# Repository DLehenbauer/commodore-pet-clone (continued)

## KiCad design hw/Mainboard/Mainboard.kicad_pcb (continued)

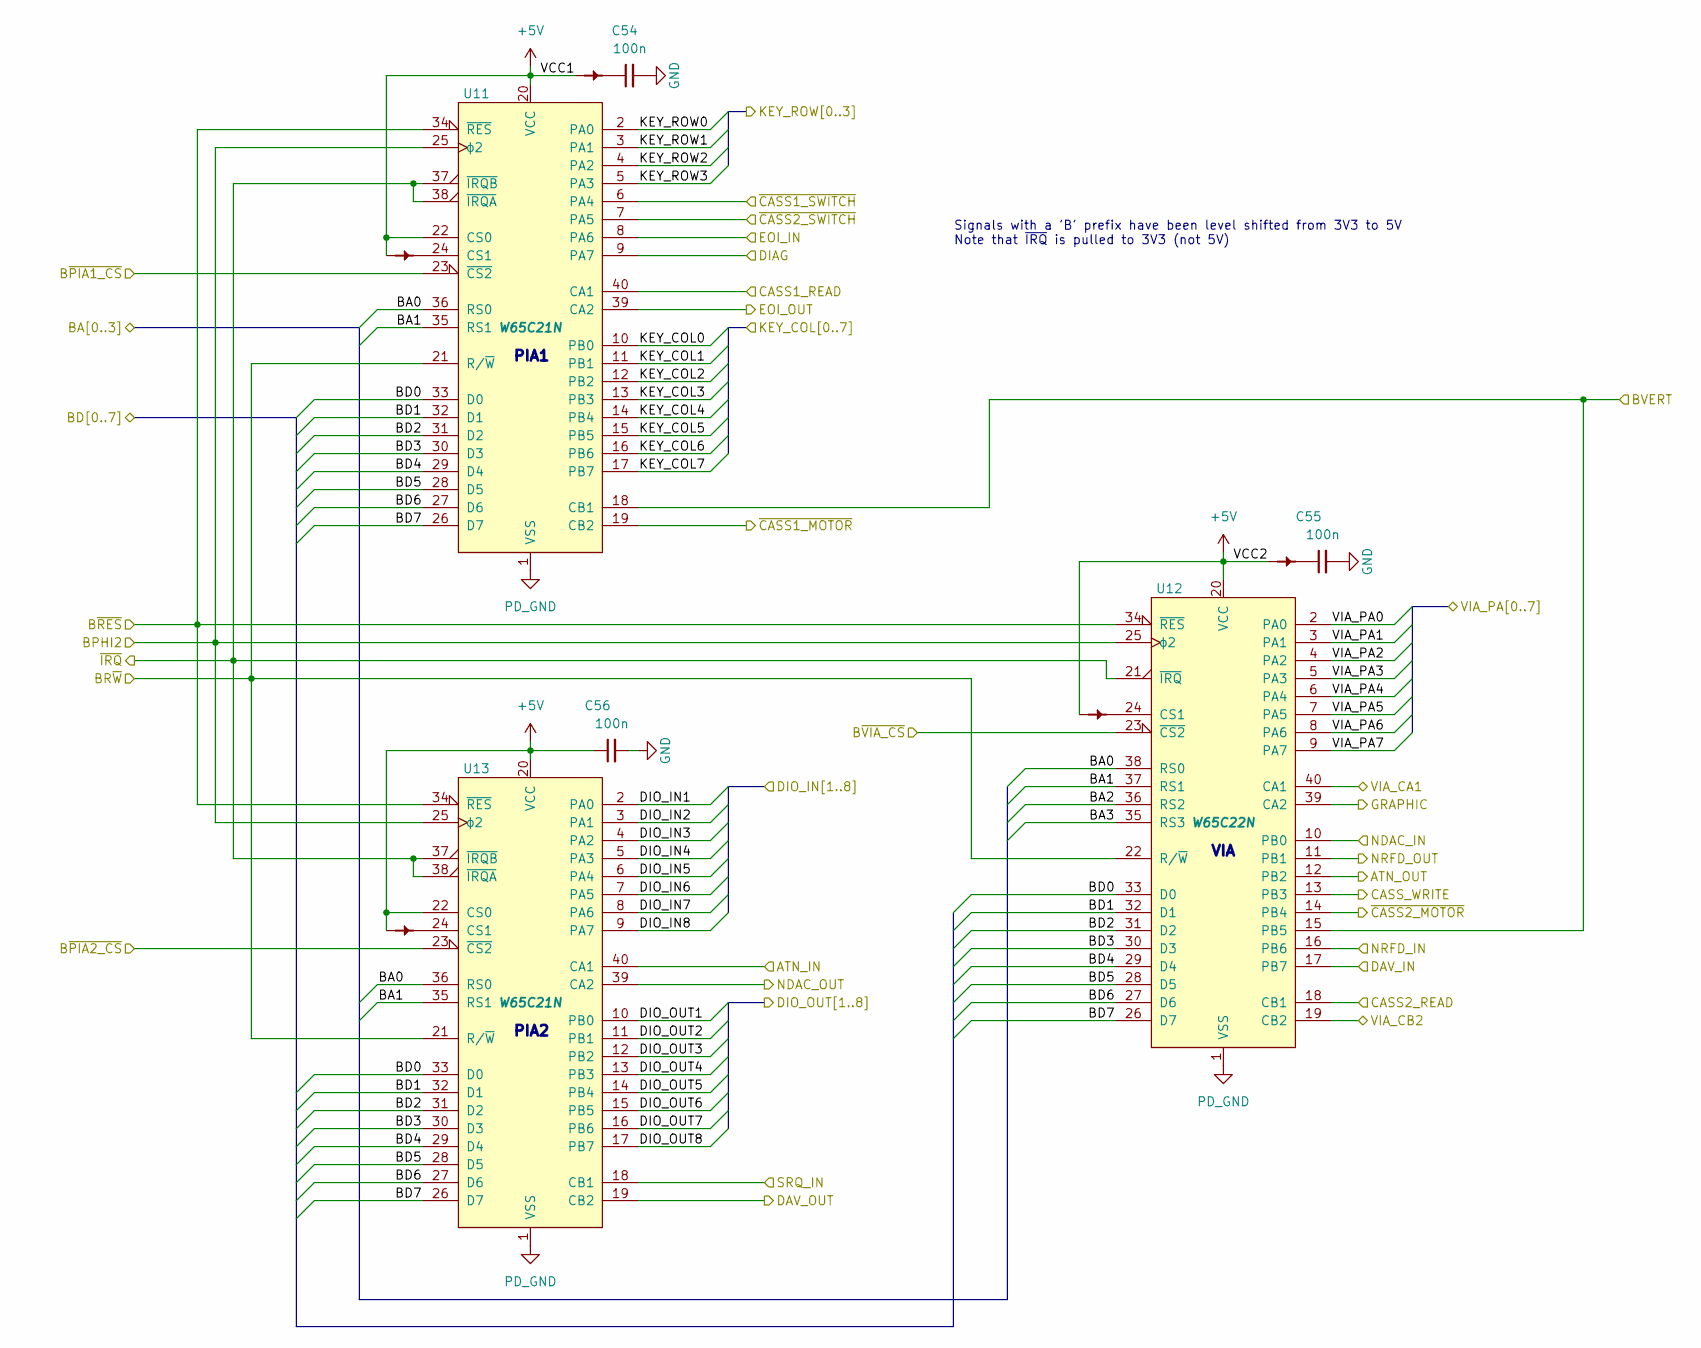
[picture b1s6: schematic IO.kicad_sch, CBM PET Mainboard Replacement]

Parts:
C54, C55, C56: 100n; C_0402_1005Metric; LCSC C307331
PT31, PT32, PT33, PT34, PT35: PowerTie_2; NetTie-2_SMD_Pad_1.6_to_0.4mm
U11, U13: W65C21N; DIP-40_W15.24mm_Socket; MOUSER 955-W65C21N6TPG-14,571-1-2199299-5
U12: W65C22N; DIP-40_W15.24mm_Socket; MOUSER 955-W65C22N6TPG-14,571-1-2199299-5

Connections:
+5V: C56.1, PT31.1, PT32.1, PT33.1, PT34.1, PT35.1, U11.20 (VCC), U11.22 (CS0), U12.20 (VCC), U13.20 (VCC), U13.22 (CS0); also elsewhere on the board
/CASS/CASS1_READ: U11.40 (CA1); also elsewhere on the board
/CASS/CASS2_READ: U12.18 (CB1); also elsewhere on the board
/CASS/CASS_WRITE: U12.13 (PB3); also elsewhere on the board
/CASS/~CASS1_MOTOR: U11.19 (CB2); also elsewhere on the board
/CASS/~CASS1_SWITCH: U11.6 (PA4); also elsewhere on the board
/CASS/~CASS2_MOTOR: U12.14 (PB4); also elsewhere on the board
/CASS/~CASS2_SWITCH: U11.7 (PA5); also elsewhere on the board
/IEEE/ATN_IN: U13.40 (CA1); also elsewhere on the board
/IEEE/ATN_OUT: U12.12 (PB2); also elsewhere on the board
/IEEE/DAV_IN: U12.17 (PB7); also elsewhere on the board
/IEEE/DAV_OUT: U13.19 (CB2); also elsewhere on the board
/IEEE/DIO_IN1: U13.2 (PA0); also elsewhere on the board
/IEEE/DIO_IN2: U13.3 (PA1); also elsewhere on the board
/IEEE/DIO_IN3: U13.4 (PA2); also elsewhere on the board
/IEEE/DIO_IN4: U13.5 (PA3); also elsewhere on the board
/IEEE/DIO_IN5: U13.6 (PA4); also elsewhere on the board
/IEEE/DIO_IN6: U13.7 (PA5); also elsewhere on the board
/IEEE/DIO_IN7: U13.8 (PA6); also elsewhere on the board
/IEEE/DIO_IN8: U13.9 (PA7); also elsewhere on the board
/IEEE/DIO_OUT1: U13.10 (PB0); also elsewhere on the board
/IEEE/DIO_OUT2: U13.11 (PB1); also elsewhere on the board
/IEEE/DIO_OUT3: U13.12 (PB2); also elsewhere on the board
/IEEE/DIO_OUT4: U13.13 (PB3); also elsewhere on the board
/IEEE/DIO_OUT5: U13.14 (PB4); also elsewhere on the board
/IEEE/DIO_OUT6: U13.15 (PB5); also elsewhere on the board
/IEEE/DIO_OUT7: U13.16 (PB6); also elsewhere on the board
/IEEE/DIO_OUT8: U13.17 (PB7); also elsewhere on the board
/IEEE/EOI_IN: U11.8 (PA6); also elsewhere on the board
/IEEE/EOI_OUT: U11.39 (CA2); also elsewhere on the board
/IEEE/IFC_OUT: U11.34 (~RES), U12.34 (~RES), U13.34 (~RES); also elsewhere on the board
/IEEE/NDAC_IN: U12.10 (PB0); also elsewhere on the board
/IEEE/NDAC_OUT: U13.39 (CA2); also elsewhere on the board
/IEEE/NRFD_IN: U12.16 (PB6); also elsewhere on the board
/IEEE/NRFD_OUT: U12.11 (PB1); also elsewhere on the board
/IEEE/SRQ_IN: U13.18 (CB1); also elsewhere on the board
/IO/BA0: U11.36 (RS0), U12.38 (RS0), U13.36 (RS0); also elsewhere on the board
/IO/BA1: U11.35 (RS1), U12.37 (RS1), U13.35 (RS1); also elsewhere on the board
/IO/BA2: U12.36 (RS2); also elsewhere on the board
/IO/BA3: U12.35 (RS3); also elsewhere on the board
/IO/BD0: U11.33 (D0), U12.33 (D0), U13.33 (D0); also elsewhere on the board
/IO/BD1: U11.32 (D1), U12.32 (D1), U13.32 (D1); also elsewhere on the board
/IO/BD2: U11.31 (D2), U12.31 (D2), U13.31 (D2); also elsewhere on the board
/IO/BD3: U11.30 (D3), U12.30 (D3), U13.30 (D3); also elsewhere on the board
/IO/BD4: U11.29 (D4), U12.29 (D4), U13.29 (D4); also elsewhere on the board
/IO/BD5: U11.28 (D5), U12.28 (D5), U13.28 (D5); also elsewhere on the board
/IO/BD6: U11.27 (D6), U12.27 (D6), U13.27 (D6); also elsewhere on the board
/IO/BD7: U11.26 (D7), U12.26 (D7), U13.26 (D7); also elsewhere on the board
/IO/BPHI2: U11.25 (ϕ2), U12.25 (ϕ2), U13.25 (ϕ2); also elsewhere on the board
/IO/BR~W: U11.21 (R/~W), U12.22 (R/~W), U13.21 (R/~W); also elsewhere on the board
/IO/BVERT: U11.18 (CB1), U12.15 (PB5); also elsewhere on the board
/IO/B~PIA1_CS: U11.23 (~CS2); also elsewhere on the board
/IO/B~PIA2_CS: U13.23 (~CS2); also elsewhere on the board
/IO/B~VIA_CS: U12.23 (~CS2); also elsewhere on the board
/IO/DIAG: U11.9 (PA7); also elsewhere on the board
/IO/GRAPHIC: U12.39 (CA2); also elsewhere on the board
/IO/KEY_COL0: U11.10 (PB0); also elsewhere on the board
/IO/KEY_COL1: U11.11 (PB1); also elsewhere on the board
/IO/KEY_COL2: U11.12 (PB2); also elsewhere on the board
/IO/KEY_COL3: U11.13 (PB3); also elsewhere on the board
/IO/KEY_COL4: U11.14 (PB4); also elsewhere on the board
/IO/KEY_COL5: U11.15 (PB5); also elsewhere on the board
/IO/KEY_COL6: U11.16 (PB6); also elsewhere on the board
/IO/KEY_COL7: U11.17 (PB7); also elsewhere on the board
/IO/KEY_ROW0: U11.2 (PA0); also elsewhere on the board
/IO/KEY_ROW1: U11.3 (PA1); also elsewhere on the board
/IO/KEY_ROW2: U11.4 (PA2); also elsewhere on the board
/IO/KEY_ROW3: U11.5 (PA3); also elsewhere on the board
/IO/VIA_CA1: U12.40 (CA1); also elsewhere on the board
/IO/VIA_CB2: U12.19 (CB2); also elsewhere on the board
/IO/VIA_PA0: U12.2 (PA0); also elsewhere on the board
/IO/VIA_PA1: U12.3 (PA1); also elsewhere on the board
/IO/VIA_PA2: U12.4 (PA2); also elsewhere on the board
/IO/VIA_PA3: U12.5 (PA3); also elsewhere on the board
/IO/VIA_PA4: U12.6 (PA4); also elsewhere on the board
/IO/VIA_PA5: U12.7 (PA5); also elsewhere on the board
/IO/VIA_PA6: U12.8 (PA6); also elsewhere on the board
/IO/VIA_PA7: U12.9 (PA7); also elsewhere on the board
/MAGIC/FPGA/~IRQ: U11.37 (~IRQB), U11.38 (~IRQA), U12.21 (~IRQ), U13.37 (~IRQB), U13.38 (~IRQA); also elsewhere on the board
GND: C54.2, C55.2, C56.2; also elsewhere on the board
unnamed: C54.1, PT31.2
unnamed: C55.1, PT33.2
unnamed: PT32.2, U11.24 (CS1)
unnamed: PT34.2, U12.24 (CS1)
unnamed: PT35.2, U13.24 (CS1)
PD_GND: U11.1 (VSS), U12.1 (VSS), U13.1 (VSS); also elsewhere on the board

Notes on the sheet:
PIA1
PIA2
Signals with a 'B' prefix have been level shifted from 3V3 to 5V Note that ~{IRQ} is pulled to 3V3 (not 5V)
VIA

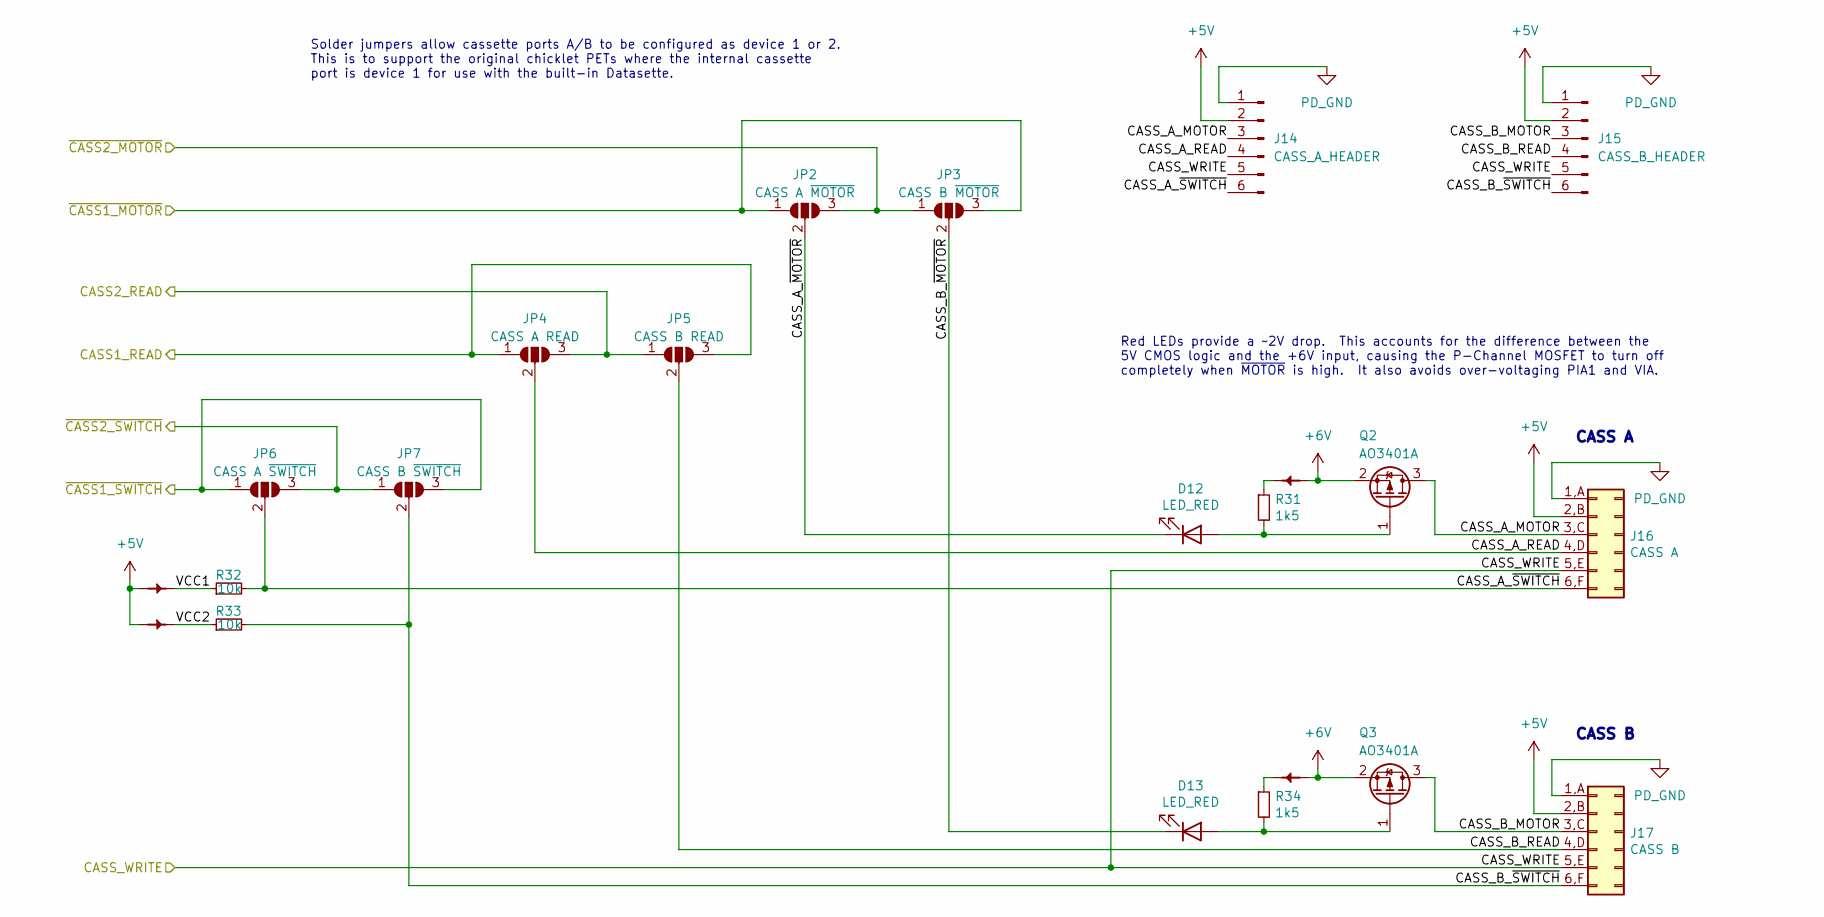
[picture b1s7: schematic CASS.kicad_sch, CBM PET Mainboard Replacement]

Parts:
D12, D13: LED_RED; LED_0603_1608Metric; LCSC C2286
J14: CASS_A_HEADER; PinHeader_1x06_P2.54mm_Vertical; MOUSER 649-1012937893602BLF
J15: CASS_B_HEADER; PinHeader_1x06_P2.54mm_Vertical; MOUSER 649-1012937893602BLF
J16: CASS A; CBM_PET_CASS_EDGE_CON_12P
J17: CASS B; CBM_PET_CASS_EDGE_CON_12P
JP2: CASS A ~{MOTOR}; SolderJumper-3_P1.3mm_Open_RoundedPad1.0x1.5mm
JP3: CASS B ~{MOTOR}; SolderJumper-3_P1.3mm_Open_RoundedPad1.0x1.5mm
JP4: CASS A READ; SolderJumper-3_P1.3mm_Open_RoundedPad1.0x1.5mm
JP5: CASS B READ; SolderJumper-3_P1.3mm_Open_RoundedPad1.0x1.5mm
JP6: CASS A ~{SWITCH}; SolderJumper-3_P1.3mm_Open_RoundedPad1.0x1.5mm
JP7: CASS B ~{SWITCH}; SolderJumper-3_P1.3mm_Open_RoundedPad1.0x1.5mm
PT38, PT39, PT40, PT41: PowerTie_2; NetTie-2_SMD_Pad_1.6_to_0.4mm
Q2, Q3: AO3401A; SOT-23_L2.9-W1.3-P1.90-LS2.4-BR; LCSC C15127
R31, R34: 1k5; R_0402_1005Metric; LCSC C25867
R32, R33: 10k; R_0402_1005Metric; LCSC C25744

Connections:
+5V: J14.2, J15.2, J16.2,B (+5V), J17.2,B (+5V), PT39.1, PT40.1; also elsewhere on the board
+6V: PT38.1, PT41.1, Q2.2 (S), Q3.2 (S); also elsewhere on the board
/CASS/CASS1_READ: JP4.1 (A), JP5.3 (B); also elsewhere on the board
/CASS/CASS2_READ: JP4.3 (B), JP5.1 (A); also elsewhere on the board
/CASS/CASS_A_MOTOR: J14.3, J16.3,C (MOTOR), Q2.3 (D)
/CASS/CASS_A_READ: J14.4, J16.4,D (READ), JP4.2 (C)
/CASS/CASS_A_~MOTOR: D12.1 (K), JP2.2 (C)
/CASS/CASS_A_~SWITCH: J14.6, J16.6,F (SWITCH), JP6.2 (C), R32.2
/CASS/CASS_B_MOTOR: J15.3, J17.3,C (MOTOR), Q3.3 (D)
/CASS/CASS_B_READ: J15.4, J17.4,D (READ), JP5.2 (C)
/CASS/CASS_B_~MOTOR: D13.1 (K), JP3.2 (C)
/CASS/CASS_B_~SWITCH: J15.6, J17.6,F (SWITCH), JP7.2 (C), R33.2
/CASS/CASS_WRITE: J14.5, J15.5, J16.5,E (WRITE), J17.5,E (WRITE); also elsewhere on the board
/CASS/VCC1: PT39.2, R32.1
/CASS/VCC2: PT40.2, R33.1
/CASS/~CASS1_MOTOR: JP2.1 (A), JP3.3 (B); also elsewhere on the board
/CASS/~CASS1_SWITCH: JP6.1 (A), JP7.3 (B); also elsewhere on the board
/CASS/~CASS2_MOTOR: JP2.3 (B), JP3.1 (A); also elsewhere on the board
/CASS/~CASS2_SWITCH: JP6.3 (B), JP7.1 (A); also elsewhere on the board
unnamed: D12.2 (A), Q2.1 (G), R31.2
unnamed: D13.2 (A), Q3.1 (G), R34.2
unnamed: PT38.2, R31.1
unnamed: PT41.2, R34.1
PD_GND: J14.1, J15.1, J16.1,A (GND), J17.1,A (GND); also elsewhere on the board

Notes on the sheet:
Solder jumpers allow cassette ports A/B to be configured as device 1 or 2. This is to support the original chicklet PETs where the internal cassette port is device 1 for use with the built-in Datasette.
CASS B
Red LEDs provide a ~2V drop. This accounts for the difference between the 5V CMOS logic and the +6V input, causing the P-Channel MOSFET to turn off completely when ~{MOTOR} is high. It also avoids over-voltaging PIA1 and VIA.
CASS A

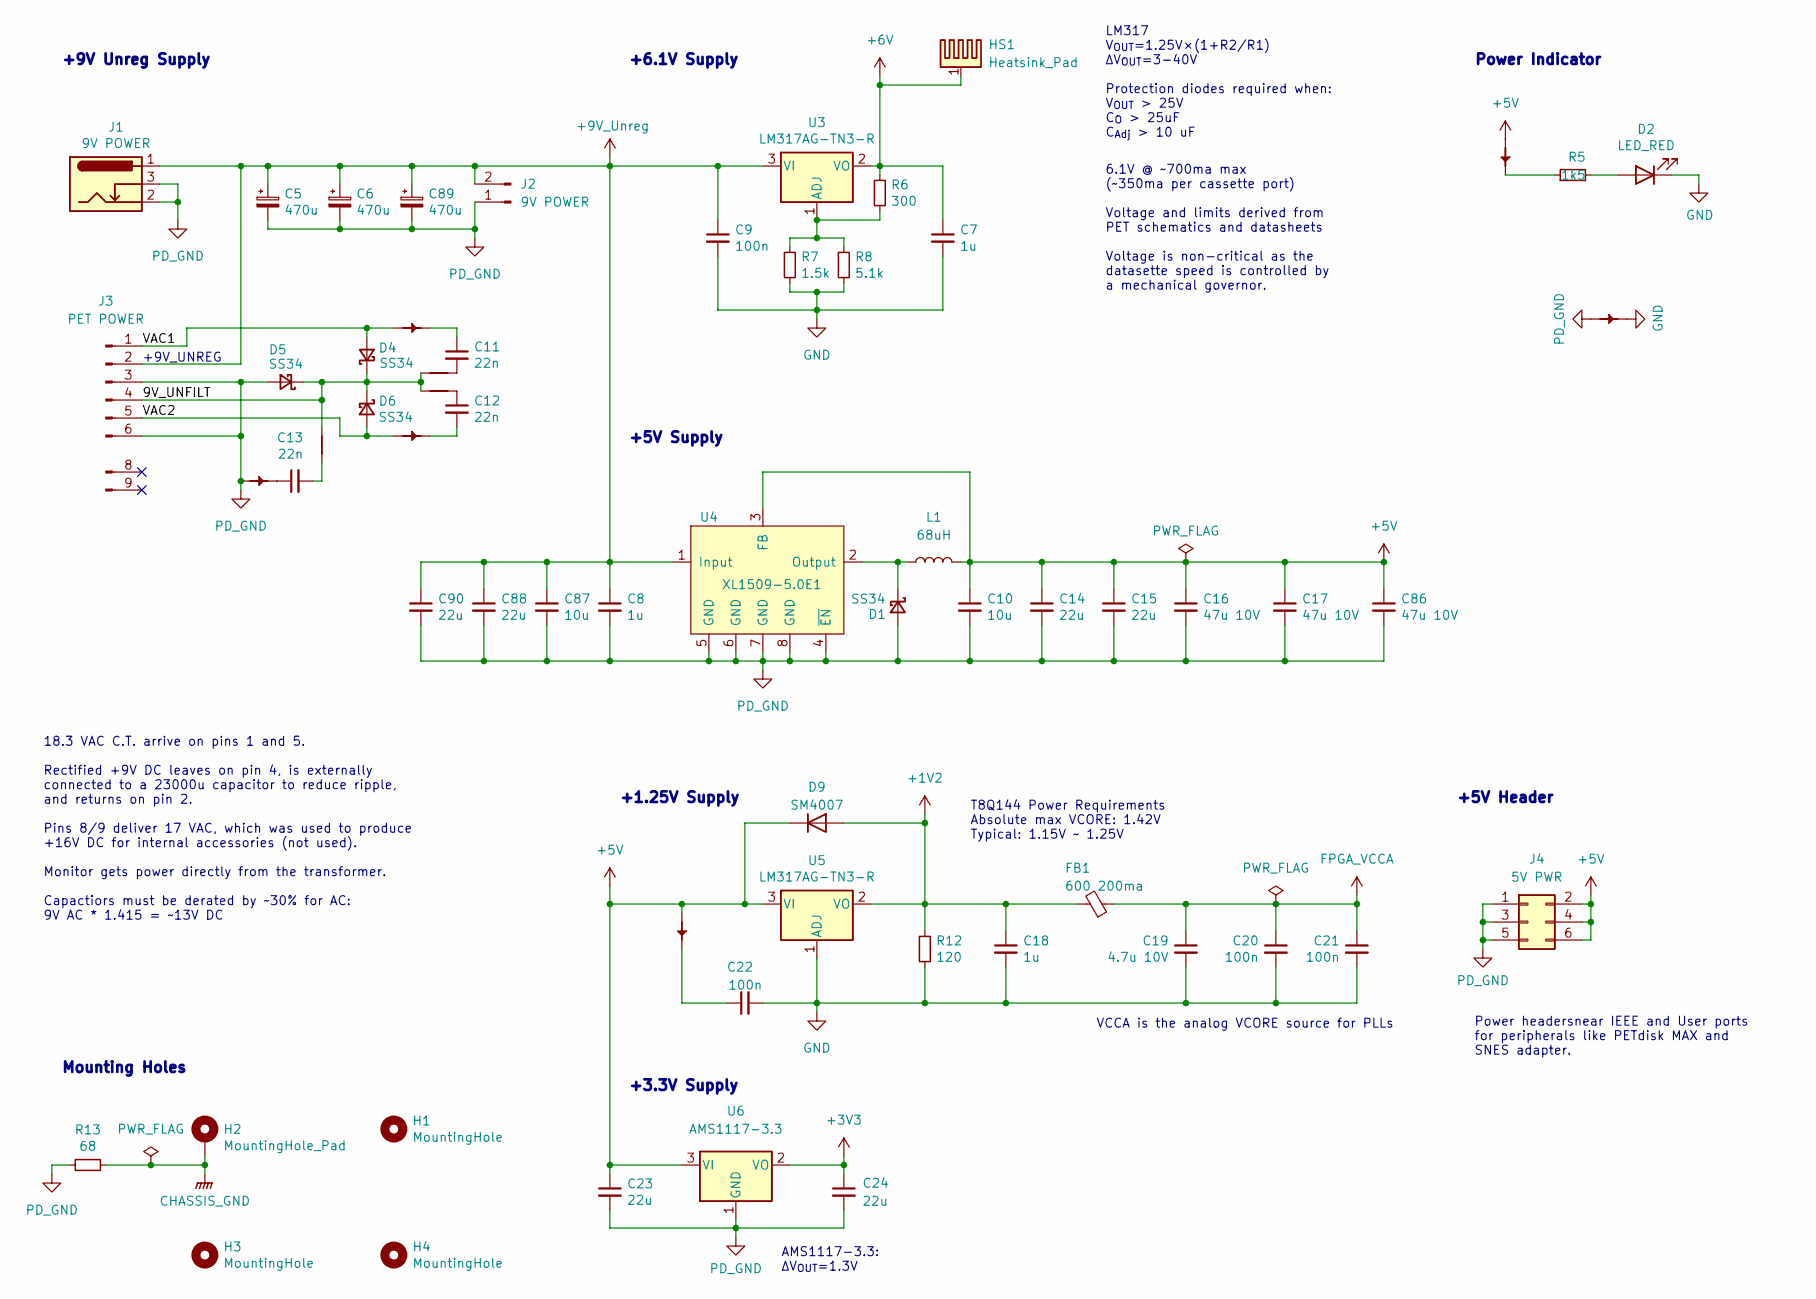
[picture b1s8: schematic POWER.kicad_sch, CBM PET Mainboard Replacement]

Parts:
C5: 470u; CP_Radial_D18.0mm_P5.00mm_P7.50mm; MPN 35YXJ470M10X16; MOUSER 232-35YXJ470M10X16
C6: 470u; CP_Radial_D16.0mm_P5.00mm_P7.50mm; MPN 35YXJ470M10X16; MOUSER 232-35YXJ470M10X16
C7, C18: 1u; C_0402_1005Metric; LCSC C52923
C8: 1u; C_0603_1608Metric; LCSC C15849
C9, C20, C21, C22: 100n; C_0402_1005Metric; LCSC C307331
C10, C87: 10u; C_0603_1608Metric; LCSC C96446
C11, C12, C13: 22n; C_0402_1005Metric; LCSC C1532
C14, C15, C23, C24, C88, C90: 22u; C_0805_2012Metric; LCSC C45783
C16, C17, C86: 47u 10V; C_1206_3216Metric; LCSC C96123
C19: 4.7u 10V; C_0402_1005Metric; LCSC C23733
C89: 470u; CP_Radial_D12.5mm_P5.00mm; MPN 35YXJ470M10X16; MOUSER 232-35YXJ470M10X16
D1, D4, D5, D6: SS34; D_SMA; LCSC C8678
D2: LED_RED; LED_0603_1608Metric; LCSC C2286
D9: SM4007; D_SOD-123F; LCSC C64898
FB1: 600 200ma; L_0603_1608Metric; LCSC C1002
H1, H3, H4: MountingHole; PET_MountingHole_4mm
H2: MountingHole_Pad; MountingHole_4mm_Pad
HS1: Heatsink_Pad; V1100SMDBL_or_573100D00000G; MPN V-1100-SMD/B-L; DIGI-KEY AE10775-ND
J1: 9V POWER; BarrelJack_Horizontal; MPN CON-SOCJ-2155; MOUSER 992-CON-SOCJ-2155
J2: 9V POWER; PinHeader_1x02_P2.54mm_Vertical; MOUSER 649-1012937893602BLF
J3: PET POWER; PET_POWER_Molex_KK-396_A-41791-0009_1x09_P3.96mm_Vertical; MOUSER 571-6403849
J4: 5V PWR; PinHeader_2x03_P2.54mm_Vertical; MOUSER 649-1012938195002BLF
L1: 68uH; IND-SMD_L11.5-W10.0_SMMS1040; LCSC C286354
PT2, PT5, PT6, PT7, PT8, PT9, PT10, PT11, PT12: PowerTie_2; NetTie-2_SMD_Pad_1.6_to_0.4mm
R5: 1k5; R_0402_1005Metric; LCSC C25867
R6: 300; R_0402_1005Metric; LCSC C25102
R7: 1.5k; R_0402_1005Metric; LCSC C25867
R8: 5.1k; R_0402_1005Metric; LCSC C25905
R12: 120; R_0402_1005Metric; LCSC C25079
R13: 68; R_0805_2012Metric; LCSC C17802
U3: LM317AG-TN3-R; TO-252-2_ThermalVias; LCSC C75510
U4: XL1509-5.0E1; SOP-8_3.9x4.9mm_P1.27mm; MPN XL1509-5.0E1; LCSC C61063
U5: LM317AG-TN3-R; TO-252-2; LCSC C75510
U6: AMS1117-3.3; SOT-223-3_TabPin2; LCSC C6186

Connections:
+1V2: C18.1, D9.2 (A), FB1.2, R12.1, U5.2 (VO); also elsewhere on the board
+3V3: C24.1, U6.2 (VO); also elsewhere on the board
+5V: C10.1, C14.1, C15.1, C16.1, C17.1, C23.1, C86.1, D9.1 (K), J4.2, J4.4, J4.6, L1.2, PT2.1, PT12.1, U4.3 (FB), U5.3 (VI), U6.3 (VI); also elsewhere on the board
+6V: C7.1, HS1.1, R6.1, U3.2 (VO); also elsewhere on the board
+9V_Unreg: C5.1, C6.1, C8.1, C9.1, C87.1, C88.1, C89.1, C90.1, J1.1, J2.2, J3.2 (9V_IN), U3.3 (VI), U4.1 (Input)
/POWER/9V_UNFILT: D4.1 (K), D5.1 (K), D6.1 (K), J3.4 (9V_OUT), PT6.1, PT7.1, PT9.1
/POWER/VAC1: D4.2 (A), J3.1 (AC1), PT5.1
/POWER/VAC2: D6.2 (A), J3.5 (AC2), PT8.1
CHASSIS_GND: H2.1, R13.1; also elsewhere on the board
FPGA_VCCA: C19.1, C20.1, C21.1, FB1.1; also elsewhere on the board
GND: C7.2, C9.2, C18.2, C19.2, C20.2, C21.2, C22.2, D2.1 (K), PT11.2, R7.2, R8.2, R12.2, U5.1 (ADJ); also elsewhere on the board
unnamed: C11.1, PT5.2
unnamed: C11.2, PT6.2
unnamed: C12.1, PT7.2
unnamed: C12.2, PT8.2
unnamed: C13.1, PT10.2
unnamed: C13.2, PT9.2
unnamed: C22.1, PT12.2
unnamed: D1.1 (K), L1.1, U4.2 (Output)
unnamed: D2.2 (A), R5.2
unnamed: PT2.2, R5.1
unnamed: R6.2, R7.1, R8.1, U3.1 (ADJ)
PD_GND: C5.2, C6.2, C8.2, C10.2, C14.2, C15.2, C16.2, C17.2, C23.2, C24.2, C86.2, C87.2, C88.2, C89.2, C90.2, D1.2 (A), D5.2 (A), J1.2, J1.3, J2.1, J3.3 (GND), J3.6 (GND), J4.1, J4.3, J4.5, PT10.1, PT11.1, R13.2, U4.4 (~EN), U4.5 (GND), U4.6 (GND), U4.7 (GND), U4.8 (GND), U6.1 (GND); also elsewhere on the board

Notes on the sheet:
T8Q144 Power Requirements Absolute max VCORE: 1.42V Typical: 1.15V ~ 1.25V
18.3 VAC C.T. arrive on pins 1 and 5. Rectified +9V DC leaves on pin 4, is externally connected to a 23000u capacitor to reduce ripple, and returns on pin 2. Pins 8/9 deliver 17 VAC, which was used to produce +16V DC for internal accessories (not used). Monitor gets power directly from the transfor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
Power Indicator
+9V_UNREG
+9V Unreg Supply
+6.1V Supply
+5V Header
VCCA is the analog VCORE source for PLLs
AMS1117-3.3: ΔV_{OUT}=1.3V
+5V Supply
Mounting Holes
Power headersnear IEEE and User ports for peripherals like PETdisk MAX and SNES adapter.
+1.25V Supply
+3.3V Supply
6.1V @ ~700ma max (~350ma per cassette port) Voltage and limits derived from PET schematics and datasheets Voltage is non-critical as the datasette speed is controlled by a mechanical governor.
LM317 V_{OUT}=1.25V×(1+R2/R1) ΔV_{OUT}=3-40V Protection diodes required when: V_{OUT} > 25V C_{O} > 25uF C_{Adj} > 10 uF

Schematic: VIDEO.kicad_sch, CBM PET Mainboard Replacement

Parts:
J21: VIDEO; PET_Video; MOUSER 649-1012937893603BLF

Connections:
/IO/BVERT: J21.3 (VERT); also elsewhere on the board
/MAGIC/BHORIZ: J21.5 (HORIZ); also elsewhere on the board
/MAGIC/BVIDEO: J21.1 (GND); also elsewhere on the board
PD_GND: J21.2 (GND), J21.4 (GND), J21.7 (VIDEO); also elsewhere on the board

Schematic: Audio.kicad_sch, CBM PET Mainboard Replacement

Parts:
C63: 100n; C_0402_1005Metric; LCSC C307331
C64: 47u 10V; C_1206_3216Metric; LCSC C96123
C65: 47n; C_0603_1608Metric; LCSC C1622
C66: 1u; C_0402_1005Metric; LCSC C52923
C67: 22n; C_0402_1005Metric; LCSC C1532
J20: SJ-43504-SMT-TR; CUI_SJ-43504-SMT-TR; MOUSER 490-SJ-43504-SMT-TR
LS1: Speaker; AT1220TT9R; MOUSER 665-AT1220TT9R
PT44, PT45, PT46: PowerTie_2; NetTie-2_SMD_Pad_1.6_to_0.4mm
R35: 4k7; R_0805_2012Metric_Pad1.20x1.40mm_HandSolder; LCSC C17673
R36: 12k; R_0805_2012Metric_Pad1.20x1.40mm_HandSolder; LCSC C17444
R37: 10; R_0805_2012Metric_Pad1.20x1.40mm_HandSolder; LCSC C17415
U20: LM386; DIP-8_W7.62mm; MOUSER 926-LM386N-1/NOPB

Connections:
+6V: PT44.1, U20.6 (V+); also elsewhere on the board
/MAGIC/FPGA/AUDIO: C66.1; also elsewhere on the board
GND: J20.1; also elsewhere on the board
unnamed: C63.1, PT44.2
unnamed: C63.2, PT45.2
unnamed: C64.1, C65.1, U20.5
unnamed: C64.2, LS1.1
unnamed: C65.2, R37.1
unnamed: C66.2, R36.1
unnamed: C67.1, J20.2, J20.3, R36.2
unnamed: C67.2, PT46.2
unnamed: J20.5, J20.6, R35.1, U20.3 (+)
PD_GND: LS1.2, PT45.1, PT46.1, R35.2, R37.2, U20.2 (-), U20.4 (GND); also elsewhere on the board

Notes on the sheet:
The AUDIO source is a 3.3V square wave. (It is 3.3V instead of 5V as a consequence of using the FPGA to implement the NAND gate between CB2 and DIAG to save an IC.) Line-level audio for consumer electronics targets a voltage of +/- 0.5V. This is achieved by a voltage divider where the output provid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

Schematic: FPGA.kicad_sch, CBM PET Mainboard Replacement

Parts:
C31, C34, C35, C36, C37, C38, C44, C45, C46, C47, C48, C49, C50, C51: 100n; C_0402_1005Metric; LCSC C307331
C32, C33, C42, C43: 1u; C_0402_1005Metric; LCSC C52923
C39, C40, C41, C52, C53: 10n; C_0402_1005Metric; LCSC C15195
D10: LED_GRN; LED_0603_1608Metric; LCSC C72043
D11: LED_RED; LED_0603_1608Metric; LCSC C2286
J5: PMOD1; PMOD_Socket_2x06_P2.54mm_Horizontal
J6: PMOD2; PMOD_Socket_2x06_P2.54mm_Horizontal
J7: PROG; IDC-Header_2x08_P2.54mm_Vertical; MOUSER 710-61201621621
J8: FPGA_MCU; PinHeader_2x10_P2.54mm_Vertical; MOUSER 649-1012938195002BLF
J9: BUS_EXPANSION; PinHeader_2x25_P2.54mm_Vertical
PT15, PT16, PT17, PT18, PT19, PT20, PT21, PT22, PT23, PT24, PT25, PT26, PT27, PT28, PT29: PowerTie_2; NetTie-2_SMD_Pad_0.28
PT30: PowerTie_2; NetTie-2_SMD_Pad_1.6_to_0.4mm
Q1: MMBT3904; SOT-23; LCSC C20526
R20: 10k; R_0402_1005Metric; LCSC C25744
R21, R27: 100k; R_0402_1005Metric; LCSC C25741
R22, R23, R24: 33; R_0402_1005Metric; LCSC C25105
R25: 12k 1%; R_0402_1005Metric; LCSC C25752
R26, R28: 1k; R_0402_1005Metric; LCSC C11702
RN1, RN2: 10k; R_Array_Convex_4x0603; LCSC C29718
SW3: CONFIG; SW_DIP_SPSTx02_Slide_6.7x6.64mm_W7.62mm_P2.54mm_LowProfile
U10: T8Q144C3; QFP50P2200X2200X160-144N; MPN T8Q144C3; DIGI-KEY 2134-T8Q144C3-ND

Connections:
+1V2: C32.1, C33.1, C34.1, C35.1, C36.1, C37.1, C38.1, C39.1, C40.1, C41.1, PT15.1, PT16.1, PT17.1, PT18.1, PT19.1, PT20.1, PT22.1; also elsewhere on the board
+3V3: C42.1, C43.1, C44.1, C45.1, C46.1, C47.1, C48.1, C49.1, C50.1, C51.1, C52.1, C53.1, J5.6, J5.12, J6.6, J6.12, J8.2, J9.3, PT21.1, PT23.1, PT24.1, PT25.1, PT26.1, PT27.1, PT28.1, PT29.1, R20.2, R26.2, R28.2, RN1.5 (R4.2), RN1.6 (R3.2), RN1.7 (R2.2), RN1.8 (R1.2), RN2.5 (R4.2), RN2.6 (R3.2), RN2.7 (R2.2), RN2.8 (R1.2); also elsewhere on the board
+5V: J7.10, J9.2; also elsewhere on the board
/CPU \ RAM/A0: J9.15, U10.60 (GPIOB_RXN03); also elsewhere on the board
/CPU \ RAM/A1: J9.17, U10.65 (GPIOB_RXN07); also elsewhere on the board
/CPU \ RAM/A2: J9.19, U10.67 (GPIOB_RXP10); also elsewhere on the board
/CPU \ RAM/A3: J9.21, U10.70 (GPIOB_RXP12_EXTFB0); also elsewhere on the board
/CPU \ RAM/A4: J9.23, U10.75 (GPIOR_157_PLLIN); also elsewhere on the board
/CPU \ RAM/A5: J9.25, U10.76 (GPIOR_155); also elsewhere on the board
/CPU \ RAM/A6: J9.27, U10.82 (GPIOR_138); also elsewhere on the board
/CPU \ RAM/A7: J9.29, U10.86 (GPIOR_133_CDI18); also elsewhere on the board
/CPU \ RAM/A8: J9.31, U10.89 (GPIOR_129_CTRL10); also elsewhere on the board
/CPU \ RAM/A9: J9.33, U10.92 (GPIOR_125_CLK10); also elsewhere on the board
/CPU \ RAM/A10: J9.35, U10.97 (GPIOR_122_CLK13_CDI21); also elsewhere on the board
/CPU \ RAM/A11: J9.37, U10.99 (GPIOR_116_CTRL15); also elsewhere on the board
/CPU \ RAM/A12: J9.14, U10.59 (GPIOB_RXN02); also elsewhere on the board
/CPU \ RAM/A13: J9.16, U10.61 (GPIOB_RXP03); also elsewhere on the board
/CPU \ RAM/A14: J9.18, U10.66 (GPIOB_RXP07); also elsewhere on the board
/CPU \ RAM/A15: J9.20, U10.69 (GPIOB_RXN12_EXTFB0); also elsewhere on the board
/CPU \ RAM/D0: J9.26, U10.77 (GPIOR_154); also elsewhere on the board
/CPU \ RAM/D1: J9.28, U10.83 (GPIOR_136_CDI16); also elsewhere on the board
/CPU \ RAM/D2: J9.30, U10.87 (GPIOR_132_CDI19); also elsewhere on the board
/CPU \ RAM/D3: J9.32, U10.90 (GPIOR_128_CTRL11); also elsewhere on the board
/CPU \ RAM/D4: J9.34, U10.93 (GPIOR_123_CLK12_CDI20); also elsewhere on the board
/CPU \ RAM/D5: J9.36, U10.98 (GPIOR_117_CTRL14); also elsewhere on the board
/CPU \ RAM/D6: J9.38, U10.100 (GPIOR_113_CDI22); also elsewhere on the board
/CPU \ RAM/D7: J9.40, U10.101 (GPIOR_112_CDI23); also elsewhere on the board
/CPU \ RAM/RAM_A10: U10.84 (GPIOR_135_CDI17); also elsewhere on the board
/CPU \ RAM/RAM_A11: U10.81 (GPIOR_139); also elsewhere on the board
/CPU \ RAM/RAM_A15: U10.68 (GPIOB_RXN10); also elsewhere on the board
/CPU \ RAM/RAM_A16: J9.22, U10.71 (GPIOB_CLKP0); also elsewhere on the board
/CPU \ RAM/~NMI: J9.11, U10.55 (GPIOB_RXP00); also elsewhere on the board
/CPU \ RAM/~RES: J9.4, U10.42 (GPIOB_TXP04); also elsewhere on the board
/MAGIC/FPGA/AUDIO: J8.3, U10.33 (GPIOL_05_CSO); also elsewhere on the board
/MAGIC/FPGA/BE: J9.9, U10.48 (GPIOB_TXN09); also elsewhere on the board
/MAGIC/FPGA/CBUS0: J9.42, RN2.3 (R3.1), U10.78 (GPIOR_151_CBUS0)
/MAGIC/FPGA/CBUS1: J9.43, RN2.2 (R2.1), U10.79 (GPIOR_150_CBUS1)
/MAGIC/FPGA/CBUS2: J9.44, RN2.1 (R1.1), U10.80 (GPIOR_149_CBUS2)
/MAGIC/FPGA/CDONE: J7.16, R27.2, RN1.4 (R4.1), U10.34 (CDONE)
/MAGIC/FPGA/CEC: J8.20, U10.6 (GPIOL_46); also elsewhere on the board
/MAGIC/FPGA/CSI: J8.4, R20.1, U10.32 (GPIOL_04_CSI)
/MAGIC/FPGA/DIAG: U10.38 (GPIOB_TXP00); also elsewhere on the board
/MAGIC/FPGA/FPGA_CLK: U10.132 (GPIOL_74_PLLIN0); also elsewhere on the board
/MAGIC/FPGA/FPGA_SPI0_TX: R22.2, U10.28 (GPIOL_09_CDI1)
/MAGIC/FPGA/FPGA_SPI1_TX: R23.2, U10.7 (GPIOL_41_CDI9)
/MAGIC/FPGA/FPGA_SPI1_~READY: R24.2, U10.16 (GPIOL_22_CTRL2)
/MAGIC/FPGA/GRAPHICS: U10.40 (GPIOB_TXP02); also elsewhere on the board
/MAGIC/FPGA/HOLD: J7.15
/MAGIC/FPGA/I2C0_SCL: J8.11, U10.15 (GPIOL_24_CLK0); also elsewhere on the board
/MAGIC/FPGA/I2C0_SDA: J8.9, U10.18 (GPIOL_20_CTRL0_CDI4); also elsewhere on the board
/MAGIC/FPGA/I2C1_SCL: J8.12, U10.14 (GPIOL_25_CLK1); also elsewhere on the board
/MAGIC/FPGA/I2C1_SDA: J8.10, U10.17 (GPIOL_21_CTRL1_CDI5); also elsewhere on the board
/MAGIC/FPGA/L12: J9.49, U10.20 (GPIOL_12_CDI2)
/MAGIC/FPGA/L13: J9.50, U10.19 (GPIOL_13_CDI3)
/MAGIC/FPGA/NSTATUS: D11.1 (K), J7.11, U10.136 (GPIOL_71_NSTATUS)
/MAGIC/FPGA/PMOD1_1: J5.1, U10.118 (GPIOR_79_EXTFB1_CDI30)
/MAGIC/FPGA/PMOD1_2: J5.2, U10.123 (GPIOR_77_PLLIN1)
/MAGIC/FPGA/PMOD1_3: J5.3, U10.131 (GPIOL_75_PLLIN1)
/MAGIC/FPGA/PMOD1_4: J5.4, U10.135 (GPIOL_72_EXTFB0_CDI14)
/MAGIC/FPGA/PMOD1_5: J5.7, U10.119 (GPIOR_78_EXTFB0_CDI31)
/MAGIC/FPGA/PMOD1_6: J5.8, U10.124 (GPIOR_76_PLLIN0)
/MAGIC/FPGA/PMOD1_7: J5.9, U10.134 (GPIOL_73_EXTFB1_CDI15)
/MAGIC/FPGA/PMOD1_8: J5.10, U10.137 (GPIOL_70_CBSEL0)
/MAGIC/FPGA/PMOD2_1: J6.1, U10.139 (GPIOL_68)
/MAGIC/FPGA/PMOD2_2: J6.2, U10.141 (GPIOL_65)
/MAGIC/FPGA/PMOD2_3: J6.3, U10.144 (GPIOL_64)
/MAGIC/FPGA/PMOD2_4: J6.4, U10.3 (GPIOL_53_CDI10)
/MAGIC/FPGA/PMOD2_5: J6.7, U10.138 (GPIOL_69_CBSEL1)
/MAGIC/FPGA/PMOD2_6: J6.8, U10.140 (GPIOL_67_CDI13)
/MAGIC/FPGA/PMOD2_7: J6.9, U10.142 (GPIOL_66_CDI12)
/MAGIC/FPGA/PMOD2_8: J6.10, U10.4 (GPIOL_54_CDI11)
/MAGIC/FPGA/R94: J9.48, U10.106 (GPIOR_94_CDI27)
/MAGIC/FPGA/R95: J9.47, U10.105 (GPIOR_95_CDI26)
/MAGIC/FPGA/R104: J9.46, U10.103 (GPIOR_104_CDI25)
/MAGIC/FPGA/R105: J9.45, U10.102 (GPIOR_105_CDI24)
/MAGIC/FPGA/RDY: J9.6, U10.43 (GPIOB_TXN04); also elsewhere on the board
/MAGIC/FPGA/REF_RES: R25.2, U10.36 (REF_RES)
/MAGIC/FPGA/S1: SW3.4, U10.116 (GPIOR_81_MREFCLK)
/MAGIC/FPGA/S2: SW3.3, U10.117 (GPIOR_80)
/MAGIC/FPGA/SPI0_RX: J8.8, R22.1; also elsewhere on the board
/MAGIC/FPGA/SPI0_SCK: J8.6, U10.30 (GPIOL_01_CCK); also elsewhere on the board
/MAGIC/FPGA/SPI0_TX: J8.7, U10.29 (GPIOL_08_CDI0); also elsewhere on the board
/MAGIC/FPGA/SPI0_~CS: J7.12, J8.5, U10.31 (GPIOL_00_SS_N); also elsewhere on the board
/MAGIC/FPGA/SPI1_RX: J8.19, R23.1; also elsewhere on the board
/MAGIC/FPGA/SPI1_SCK: J8.16, U10.11 (GPIOL_31_CLK7_CDI6); also elsewhere on the board
/MAGIC/FPGA/SPI1_TX: J8.18, U10.8 (GPIOL_40_CDI8); also elsewhere on the board
/MAGIC/FPGA/SPI1_~CS: J8.17, U10.10 (GPIOL_32_CTRL4_CDI7); also elsewhere on the board
/MAGIC/FPGA/SPI1_~READY: J8.15, R24.1; also elsewhere on the board
/MAGIC/FPGA/SWCLK: J7.3; also elsewhere on the board
/MAGIC/FPGA/SWD: J7.5; also elsewhere on the board
/MAGIC/FPGA/SYNC: J9.10, U10.54 (GPIOB_TXN11); also elsewhere on the board
/MAGIC/FPGA/TCK: J7.2, RN1.1 (R1.1), U10.26 (TCK)
/MAGIC/FPGA/TDI: J7.4, RN1.2 (R2.1), U10.27 (TDI)
/MAGIC/FPGA/TDO: J7.6, U10.24 (TDO)
/MAGIC/FPGA/TMS: J7.8, RN1.3 (R3.1), U10.25 (TMS)
/MAGIC/FPGA/UART_RX: J7.7; also elsewhere on the board
/MAGIC/FPGA/UART_TX: J7.9; also elsewhere on the board
/MAGIC/FPGA/VCCIO_12: PT23.2, U10.12 (VCCIO1C_1D)
/MAGIC/FPGA/VCCIO_23: PT21.2, U10.21 (VCCIO1B), U10.23 (VCCIO1A)
/MAGIC/FPGA/VCCIO_52: PT29.2, U10.51 (VCCIO4B), U10.52 (VCCIO4B)
/MAGIC/FPGA/VCCIO_62: PT28.2, U10.62 (VCCIO4A), U10.63 (VCCIO4A)
/MAGIC/FPGA/VCCIO_88: PT27.2, U10.88 (VCCIO3E), U10.91 (VCCIO3D)
/MAGIC/FPGA/VCCIO_95: PT26.2, U10.95 (VCCIO3B_3C)
/MAGIC/FPGA/VCCIO_122: PT25.2, U10.122 (VCCIO3A)
/MAGIC/FPGA/VCCIO_143: PT24.2, U10.143 (VCCIO1E)
/MAGIC/FPGA/VCC_13: PT15.2, U10.13 (VCC)
/MAGIC/FPGA/VCC_22: PT16.2, U10.22 (VCC)
/MAGIC/FPGA/VCC_49: PT17.2, U10.49 (VCC)
/MAGIC/FPGA/VCC_57: PT18.2, U10.57 (VCC)
/MAGIC/FPGA/VCC_85: PT19.2, U10.85 (VCC)
/MAGIC/FPGA/VCC_96: PT20.2, U10.96 (VCC)
/MAGIC/FPGA/VCC_125: PT22.2, U10.125 (VCC), U10.128 (VCC), U10.130 (VCC)
/MAGIC/FPGA/VIA_CB2: U10.39 (GPIOB_TXN00); also elsewhere on the board
/MAGIC/FPGA/VSS: PT30.2, U10.1 (GND), U10.5 (GND), U10.9 (GND), U10.37 (GND), U10.44 (GND), U10.50 (GND), U10.64 (GND), U10.94 (GND), U10.104 (GND), U10.108 (GND), U10.120 (GND), U10.121 (GND), U10.126 (GND), U10.127 (GND), U10.129 (GND), U10.133 (GND)
/MAGIC/FPGA/~CRESET: C31.1, J7.14, R21.1, U10.35 (~CRESET); also elsewhere on the board
/MAGIC/FPGA/~IRQ: J9.8, U10.47 (GPIOB_TXP09); also elsewhere on the board
/MAGIC/FPGA/~ML: U10.53 (GPIOB_TXP11); also elsewhere on the board
/MAGIC/FPGA/~RAM_OE: U10.72 (GPIOB_CLKN0); also elsewhere on the board
/MAGIC/FPGA/~RAM_WE: U10.58 (GPIOB_RXP02); also elsewhere on the board
/MAGIC/FPGA/~SO: J9.5, U10.45 (GPIOB_TXP06); also elsewhere on the board
/MAGIC/FPGA/~SPI_ENA: J7.13; also elsewhere on the board
/MAGIC/FPGA/~TEST: J9.41, RN2.4 (R4.1), U10.74 (GPIOR_158_TEST_N)
/MAGIC/FPGA/~VP: U10.41 (GPIOB_TXN02); also elsewhere on the board
/MAGIC/HORIZ: U10.111 (GPIOR_85); also elsewhere on the board
/MAGIC/PHI2: J9.7, U10.46 (GPIOB_TXN06); also elsewhere on the board
/MAGIC/R~W: J9.12, U10.56 (GPIOB_RXN00); also elsewhere on the board
/MAGIC/VERT: U10.110 (GPIOR_87_CDI29); also elsewhere on the board
/MAGIC/VIDEO: U10.109 (GPIOR_88_CDI28); also elsewhere on the board
/MAGIC/~IO_OE: U10.115 (GPIOR_82); also elsewhere on the board
/MAGIC/~PIA1_CS: U10.112 (GPIOR_86); also elsewhere on the board
/MAGIC/~PIA2_CS: U10.114 (GPIOR_83); also elsewhere on the board
/MAGIC/~VIA_CS: U10.113 (GPIOR_84); also elsewhere on the board
FPGA_VCCA: U10.2 (VCCA_TL), U10.73 (VCCA_BR), U10.107 (VCCA_TR); also elsewhere on the board
GND: C31.2, C32.2, C33.2, C34.2, C35.2, C36.2, C37.2, C38.2, C39.2, C40.2, C41.2, C42.2, C43.2, C44.2, C45.2, C46.2, C47.2, C48.2, C49.2, C50.2, C51.2, C52.2, C53.2, J7.1, J8.1, J8.13, J8.14, J9.1, J9.13, J9.24, J9.39, PT30.1, Q1.2 (E), R21.2, R25.1; also elsewhere on the board
unnamed: D10.1 (K), Q1.3 (C)
unnamed: D10.2 (A), R26.1
unnamed: D11.2 (A), R28.1
unnamed: Q1.1 (B), R27.1
PD_GND: J5.5, J5.11, J6.5, J6.11, SW3.1, SW3.2; also elsewhere on the board

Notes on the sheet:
During configuration, all GPIO pins excluding LVDS as GPIO are configured in weak pull-up mode. The LVDS as GPIO pins are tri-stated without a pull-up or pull-down resistor.
BD0
BD2
BD1
NSTATUS driven low if bitstream contains wrong device ID or fails CRC check.
AD7
AD4
Pull ~{CRESET} low to reset FPGA until MCU is ready. Note that MCU drives ~{CRESET} through 10k resistor so it can be overridden by programmer when connected. Pull CSI high to enable FPGA configuration Pull TEST_N high to deactivate test mode Pull CBUS[2:0] high for SPI x1 Leave CBSEL[1:0] floating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
BD3
Minimum decoupling caps is one 100nF and one 10nF Place lowest values closest to pin.
AD5
AD6
AD3
CDONE is open drain and requires pullup to enter user mode. TDO is terminated by the programmer at the receiving end.
CDONE is an open drain output with 10k pullup. Driving LED requires a current amplifier.
